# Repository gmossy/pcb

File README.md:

# pcb

This repository contains my printed circuit board designs. I use many of the designs for my robot projects and some of the others for general purposes and smaller electronics projects.

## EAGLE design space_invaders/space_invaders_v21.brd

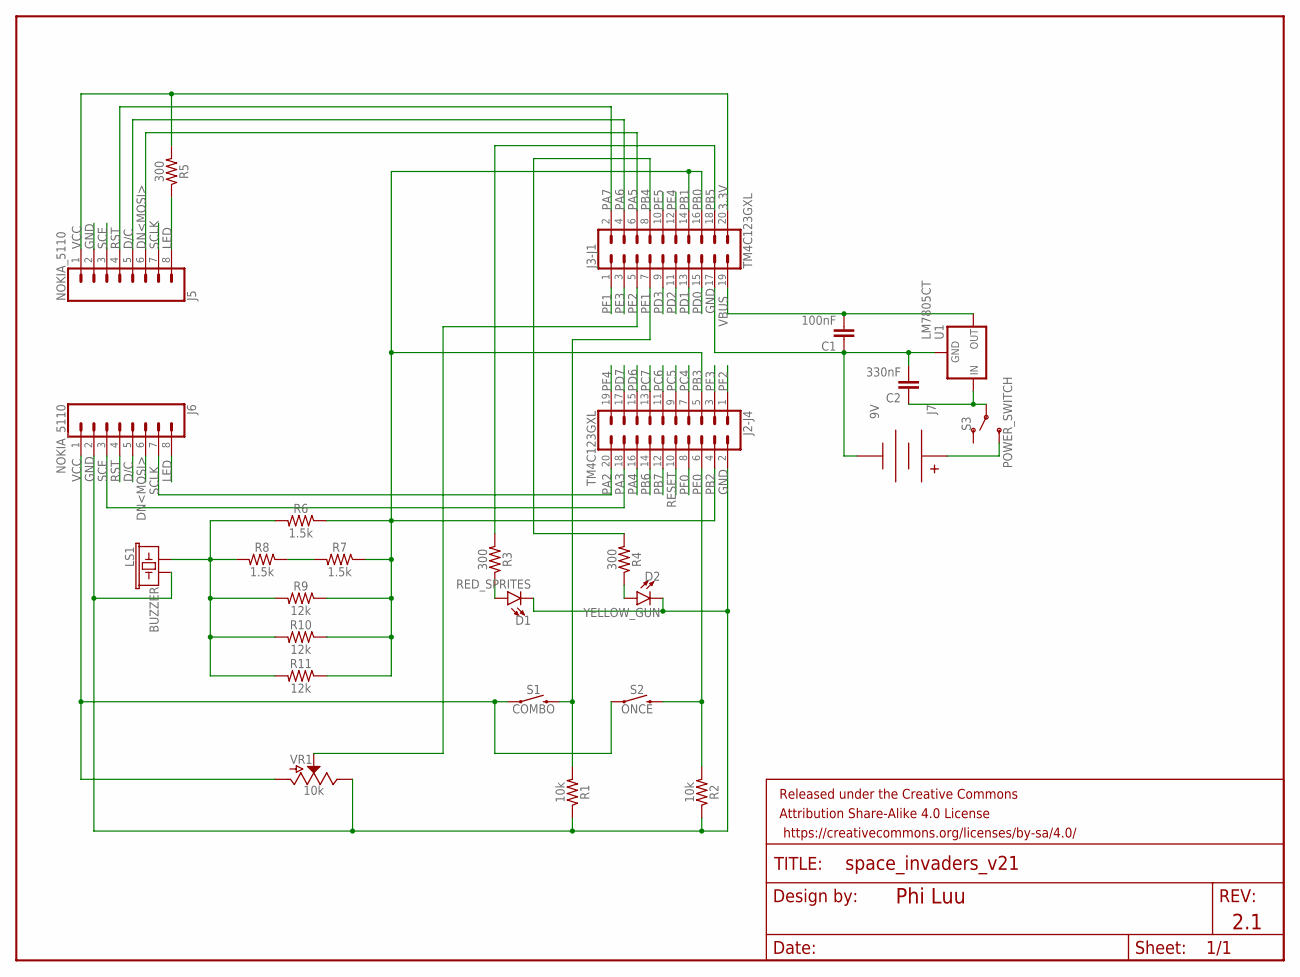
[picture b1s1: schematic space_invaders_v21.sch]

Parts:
C1: 100nF; CAP-PTH-SMALL-KIT
C2: 330nF; CAP-PTH-SMALL-KIT
D1: RED_SPRITES; LED_5MM
D2: YELLOW_GUN; LED_5MM
FRAME1: FRAME-LETTER; CREATIVE_COMMONS
J2-J4, J3-J1: TM4C123GXL; 2X10
J5, J6: NOKIA_5110; 1X08
J7: 9V; BC9VPC
LS1: BUZZER; BUZZER-12MM
R1, R2: 10k; AXIAL-0.3
R3, R4, R5: 300; AXIAL-0.3
R6, R7, R8: 1.5k; AXIAL-0.3
R9, R10, R11: 12k; AXIAL-0.3
S1: COMBO; TACTILE_SWITCH_PTH_6.0MM
S2: ONCE; TACTILE_SWITCH_PTH_6.0MM
S3: POWER_SWITCH; SWITCH_SPDT_PTH_11.6X4.0MM
U1: LM7805CT; TO220-IGO
VR1: 10k; SLIDER-MEDIUM

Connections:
3.3V: J3-J1.20, J5.1, J6.1, R5.P$2 (2), S1.1, S2.1, VR1.BOTTOM (A)
9V: J7.V+, S3.3 (S)
DAC: J2-J4.4, J2-J4.5, J3-J1.14, J3-J1.16, R6.P$1 (1), R7.P$1 (1), R9.P$1 (1), R10.P$1 (1), R11.P$1 (1)
DAC_OUT: LS1.+ (1), R6.P$2 (2), R8.P$2 (2), R9.P$2 (2), R10.P$2 (2), R11.P$2 (2)
GND: C1.1, C2.2, D1.K (C), D2.K (C), J2-J4.2, J3-J1.17, J5.2, J6.2, J7.V-, LS1.- (2), R1.P$1 (1), R2.P$1 (1), U1.GND, VR1.TOP (E)
LED: J5.8, J6.8, R5.P$1 (1)
LLED: D1.A, R3.P$1 (1)
unnamed: R7.P$2 (2), R8.P$1 (1)
PA2: J2-J4.20, J5.7, J6.7
PA3: J2-J4.18, J5.3, J6.3
PA4: J2-J4.16
PA5: J3-J1.6, J5.6, J6.6
PA6: J3-J1.4, J5.5, J6.5
PA7: J3-J1.2, J5.4, J6.4
PB4: J3-J1.8, R4.P$2 (2)
PB5: J3-J1.18, R3.P$2 (2)
PB6: J2-J4.14
PB7: J2-J4.12
PC4: J2-J4.7
PC5: J2-J4.9
PC6: J2-J4.11
PC7: J2-J4.13
PD0: J3-J1.15
PD1: J3-J1.13
PD2: J3-J1.11
PD3: J3-J1.9
PD6: J2-J4.15
PD7: J2-J4.17
PE0: J2-J4.6, R2.P$2 (2), S2.3 (2)
PE1: J3-J1.7, R1.P$2 (2), S1.3 (2)
PE2: J3-J1.5, VR1.WIPER (S)
PE3: J3-J1.3
PE4: J3-J1.12
PE5: J3-J1.10
PF0: J2-J4.8
PF1: J3-J1.1
PF2: J2-J4.1
PF3: J2-J4.3
PF4: J2-J4.19
RESET: J2-J4.10
RLED: D2.A, R4.P$1 (1)
VBUS: C1.2, J3-J1.19, U1.OUT
VIN: C2.1, S3.2, U1.IN

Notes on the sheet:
Phi Luu
2.1
PB0
PB1
PB3
VCC
RST
D/C
DN<MOSI>
SCE
SCLK
PB2

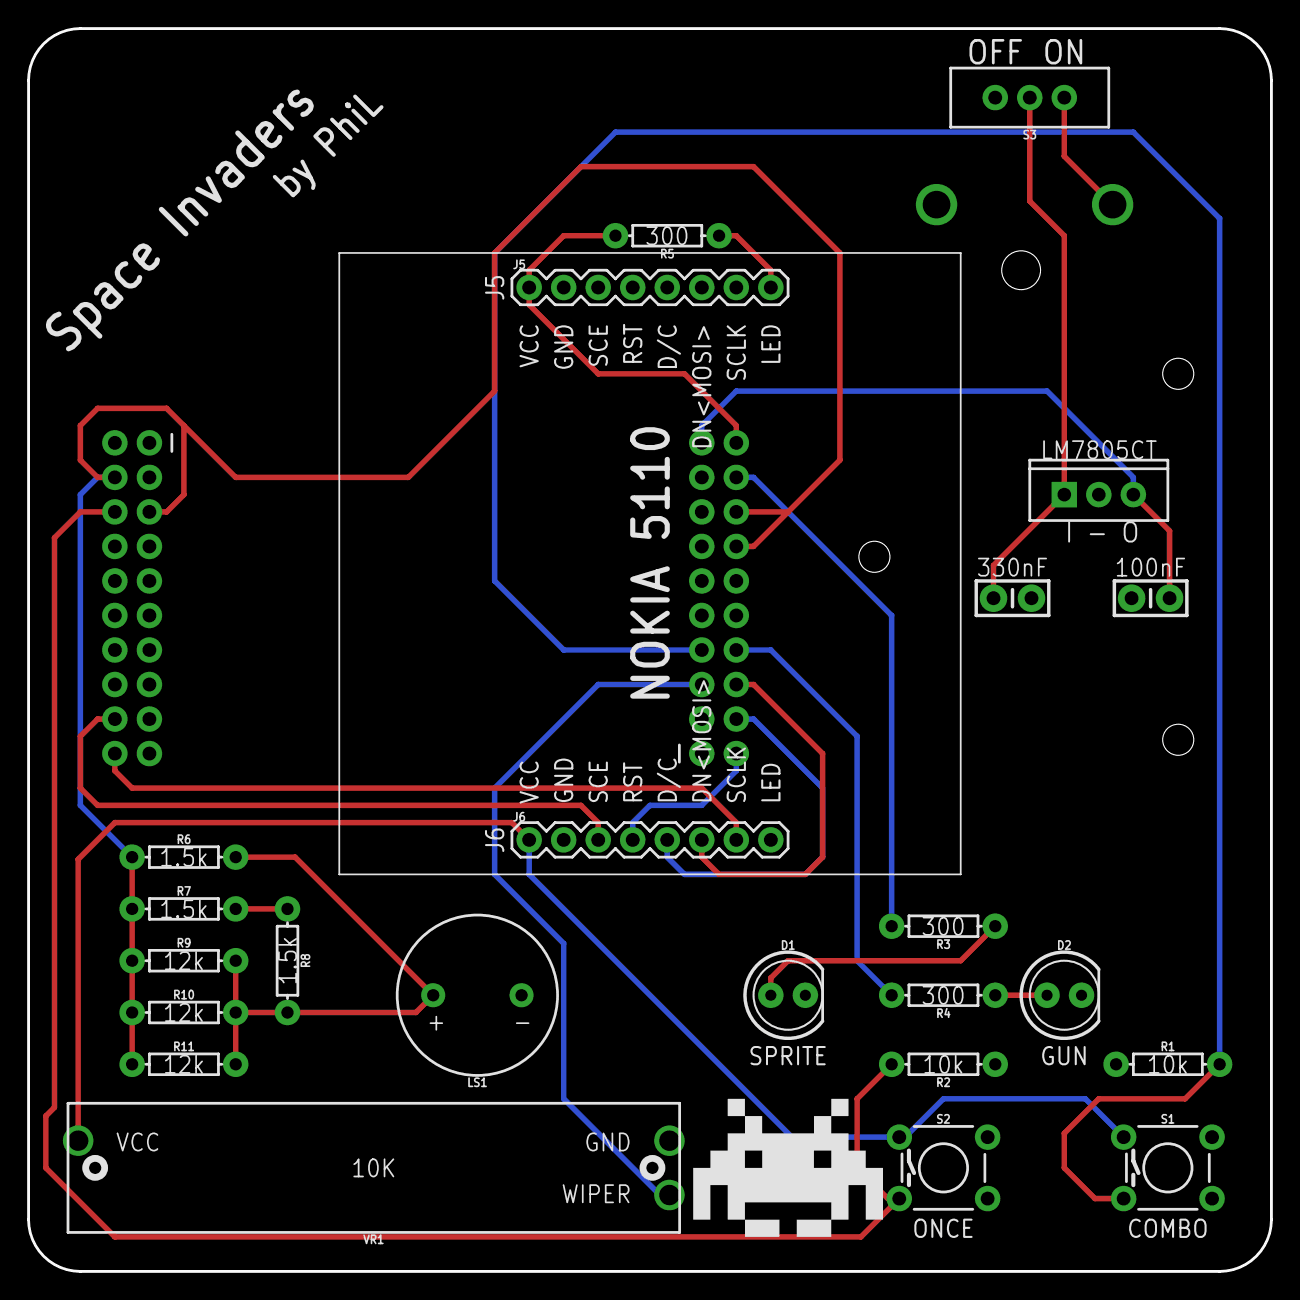
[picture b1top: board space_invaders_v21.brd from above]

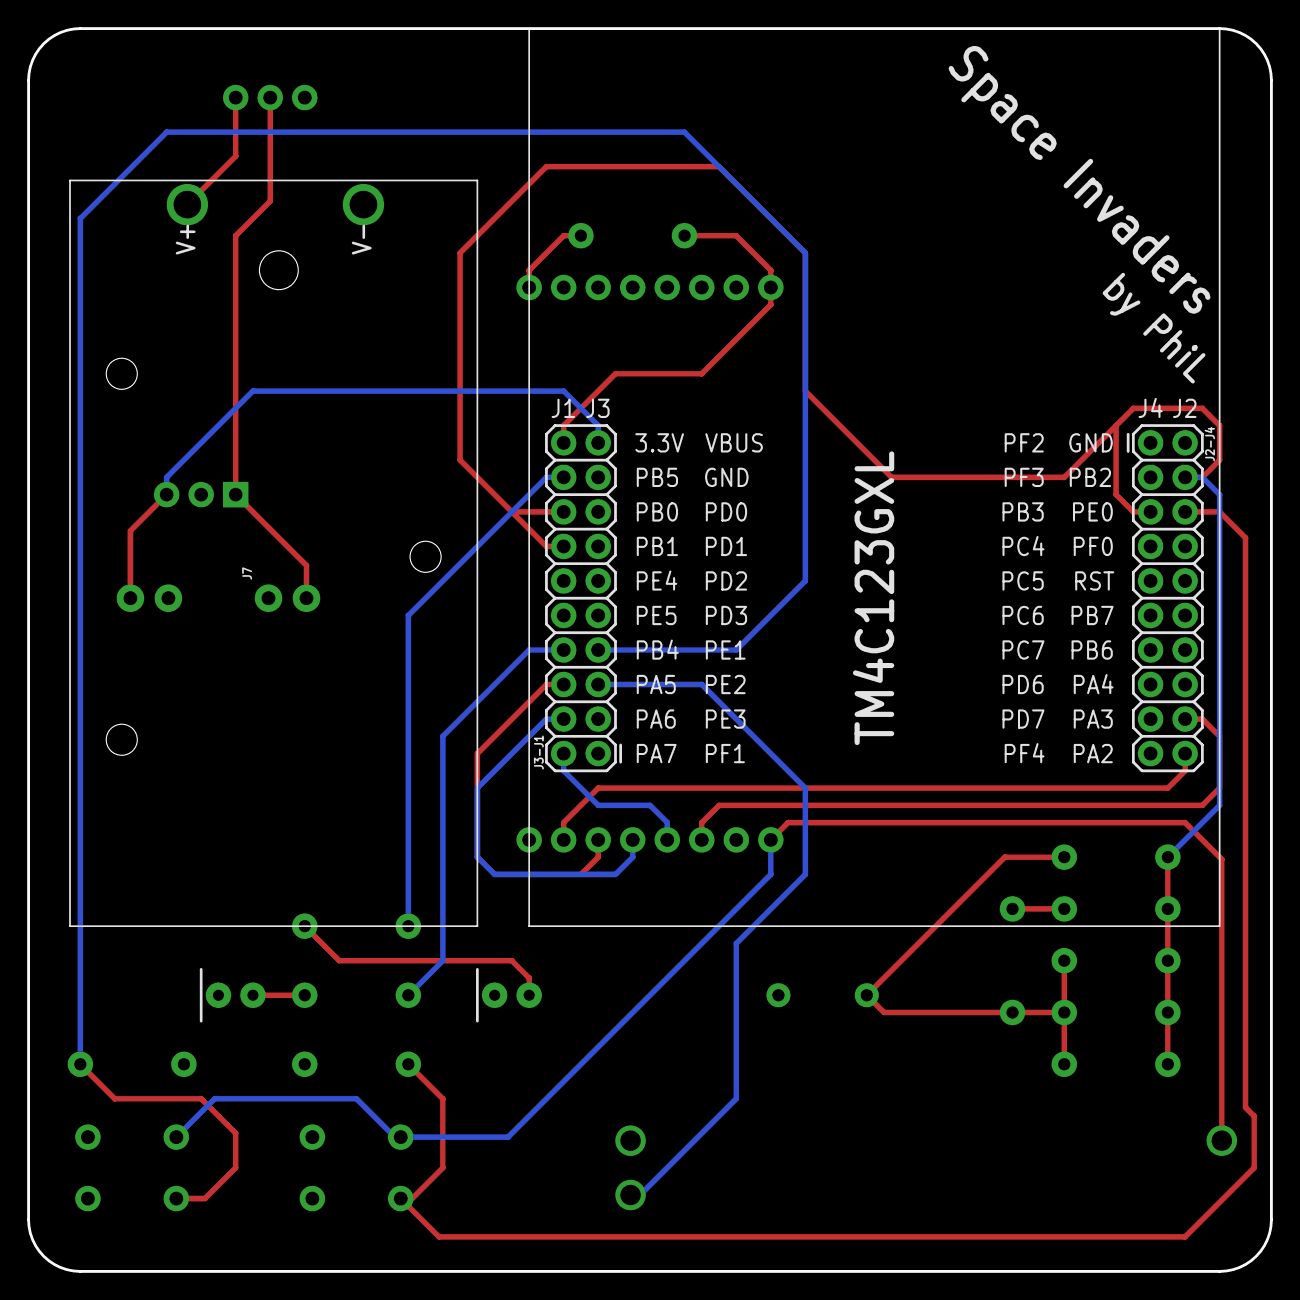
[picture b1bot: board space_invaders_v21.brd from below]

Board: 2 copper layers, 91.4 x 91.4 mm, 27 parts (3 on the bottom side), 21 nets.

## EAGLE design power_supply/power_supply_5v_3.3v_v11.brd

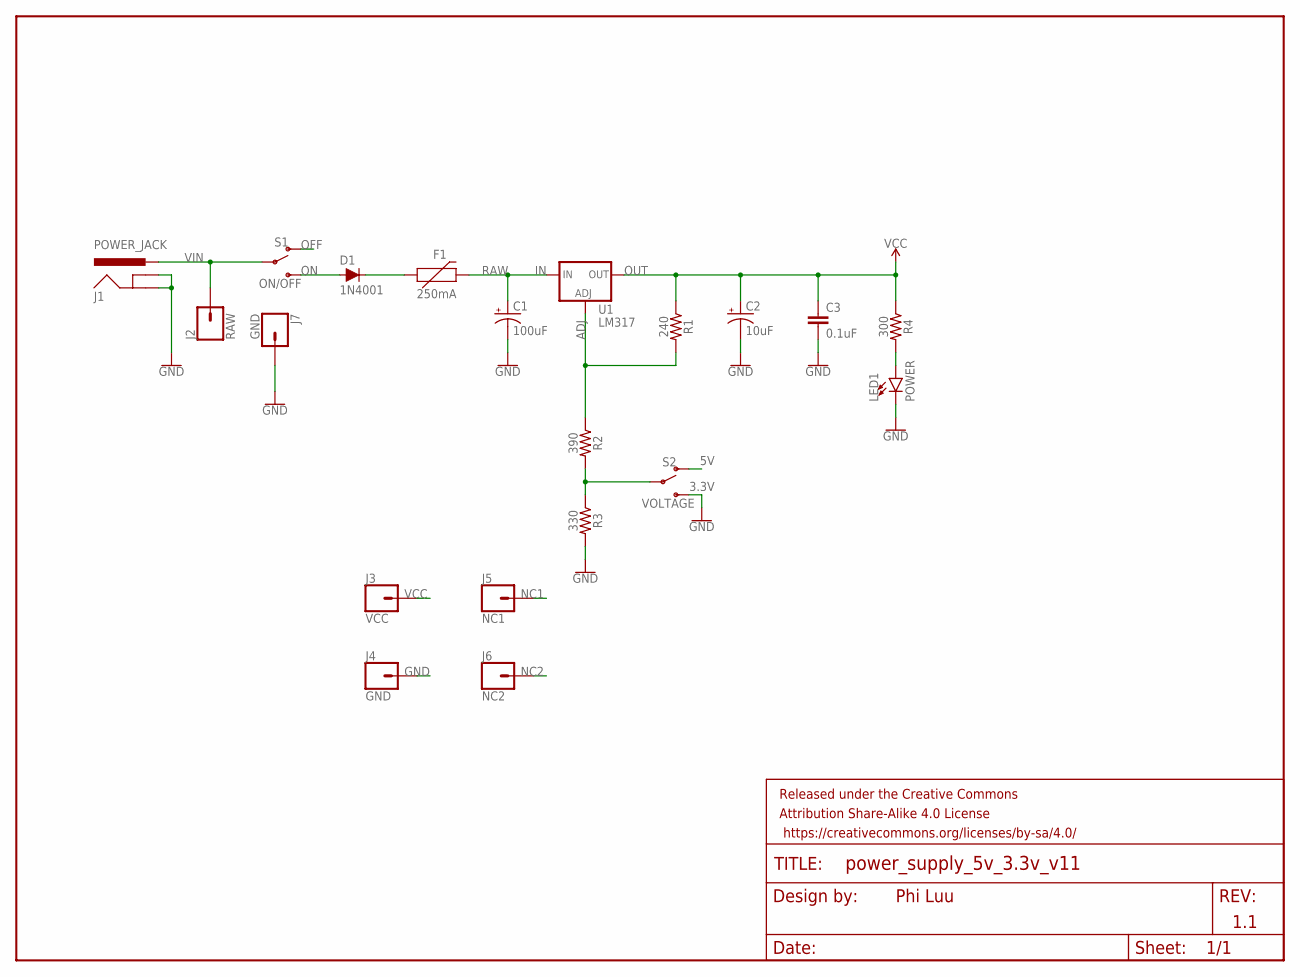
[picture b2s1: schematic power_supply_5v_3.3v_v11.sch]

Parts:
C1: 100uF; CPOL-RADIAL-2.5MM-6.5MM
C2: 10uF; CPOL-RADIAL-2.5MM-5MM
C3: 0.1uF; CAP-PTH-SMALL-KIT
D1: 1N4001; DIODE-1N4001
F1: 250mA; PTH
FRAME1: FRAME-LETTER; CREATIVE_COMMONS
J1: POWER_JACK; POWER_JACK_PTH
J2: RAW; 1X01
J3: VCC; 1X01
J4, J7: GND; 1X01
J5: NC1; 1X01
J6: NC2; 1X01
LED1: POWER; LED_5MM
R1: 240; AXIAL-0.3
R2: 390; AXIAL-0.3
R3: 330; AXIAL-0.3
R4: 300; AXIAL-0.3
S1: ON/OFF; SWITCH_SPDT_PTH_11.6X4.0MM
S2: VOLTAGE; SWITCH_SPDT_PTH_11.6X4.0MM
U1: LM317; TO220-ADJ

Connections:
5V: S2.1 (O)
ADJ: R1.P$2 (2), R2.P$1 (1), U1.ADJ
GND: C1.2 (-), C2.2 (-), C3.2, J1.GND, J1.GNDBREAK, J4.1, J7.1, LED1.K (C), R3.P$2 (2), S2.3 (S)
LED: LED1.A, R4.P$2 (2)
unnamed: D1.C, F1.P$1 (1)
unnamed: R2.P$2 (2), R3.P$1 (1), S2.2
NC1: J5.1
NC2: J6.1
OFF: S1.1 (O)
ON: D1.A, S1.3 (S)
RAW: C1.1 (+), F1.P$2 (2), U1.IN
VCC: C2.1 (+), C3.1, J3.1, R1.P$1 (1), R4.P$1 (1), U1.OUT
VIN: J1.PWR, J2.1, S1.2

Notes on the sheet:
Phi Luu
1.1
OUT
3.3V

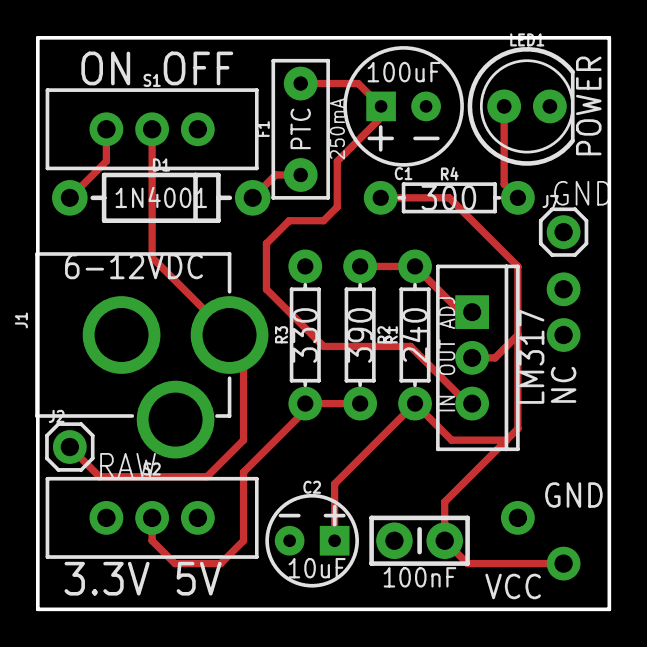
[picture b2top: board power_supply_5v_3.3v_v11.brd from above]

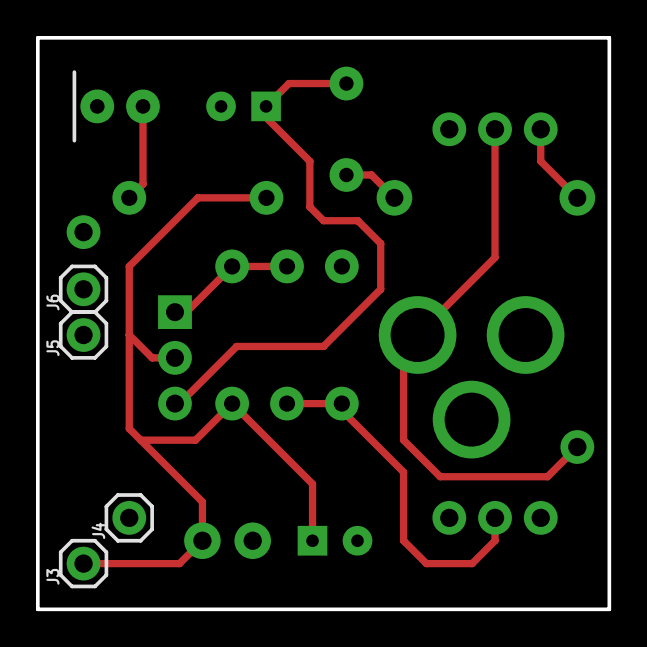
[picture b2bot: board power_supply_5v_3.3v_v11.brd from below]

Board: 2 copper layers, 31.8 x 31.8 mm, 21 parts (4 on the bottom side), 9 nets.

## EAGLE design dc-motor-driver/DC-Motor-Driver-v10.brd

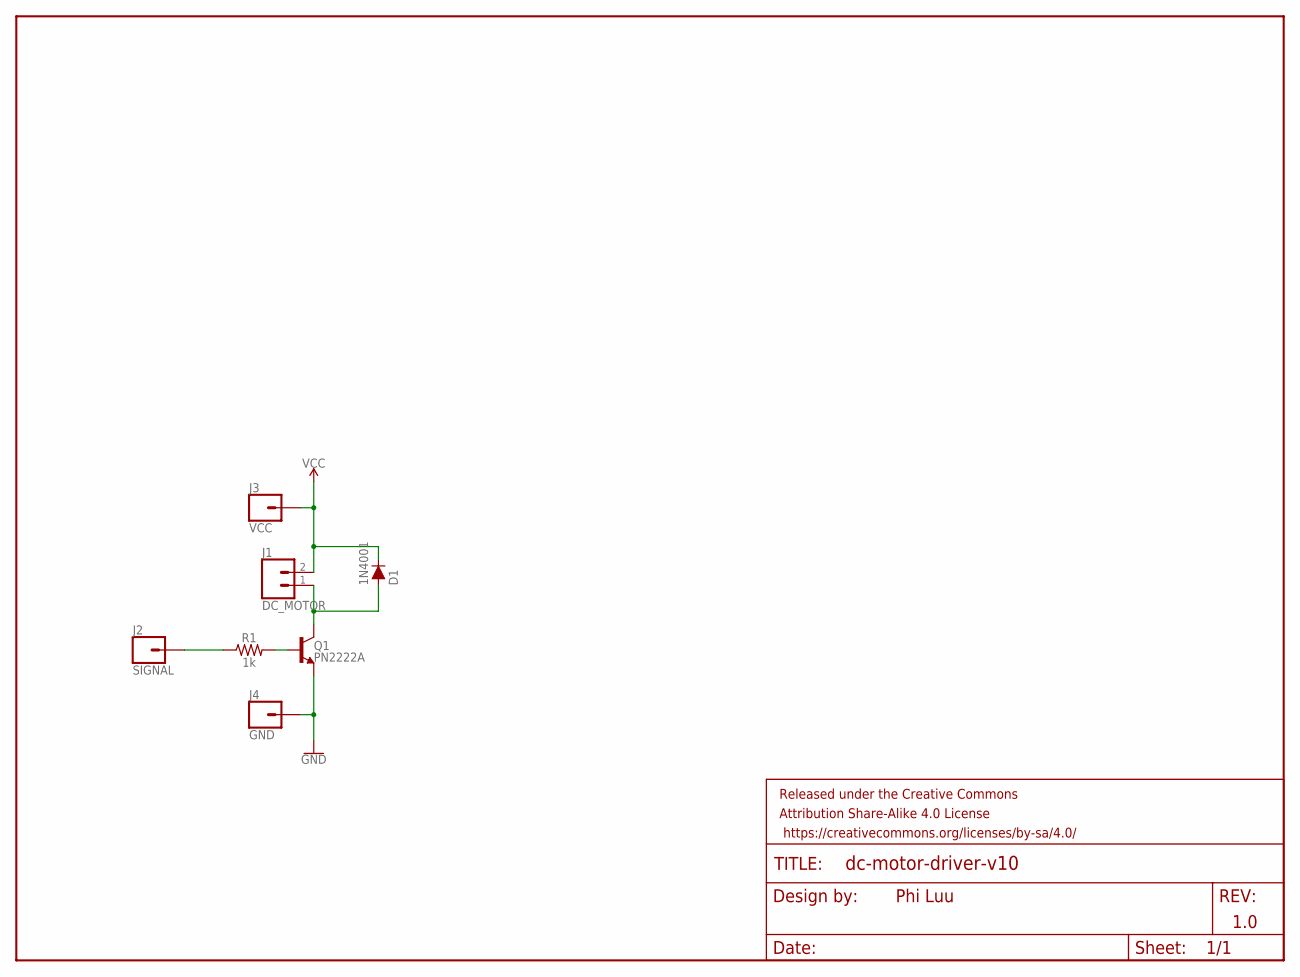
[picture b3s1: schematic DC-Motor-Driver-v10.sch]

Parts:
D1: 1N4001; DIODE-1N4001
FRAME1: FRAME-LETTER; CREATIVE_COMMONS
J1: DC_MOTOR; 1X02
J2: SIGNAL; 1X01
J3: VCC; 1X01
J4: GND; 1X01
Q1: PN2222A; TO-92
R1: 1k; AXIAL-0.3

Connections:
BASE: Q1.2 (B), R1.P$2 (2)
COLLECTOR: D1.A, J1.1, Q1.1 (C)
GND: J4.1, Q1.3 (E)
SIGNAL: J2.1, R1.P$1 (1)
VCC: D1.C, J1.2, J3.1

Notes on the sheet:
Phi Luu
1.0

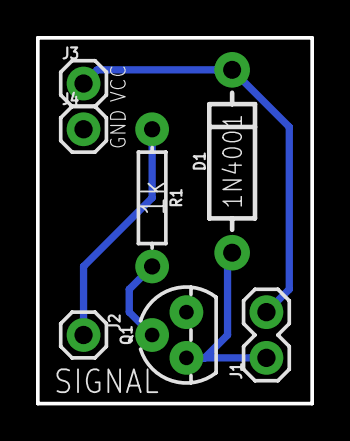
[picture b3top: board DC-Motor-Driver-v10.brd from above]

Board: 2 copper layers, 15.2 x 20.3 mm, 8 parts (0 on the bottom side), 5 nets.

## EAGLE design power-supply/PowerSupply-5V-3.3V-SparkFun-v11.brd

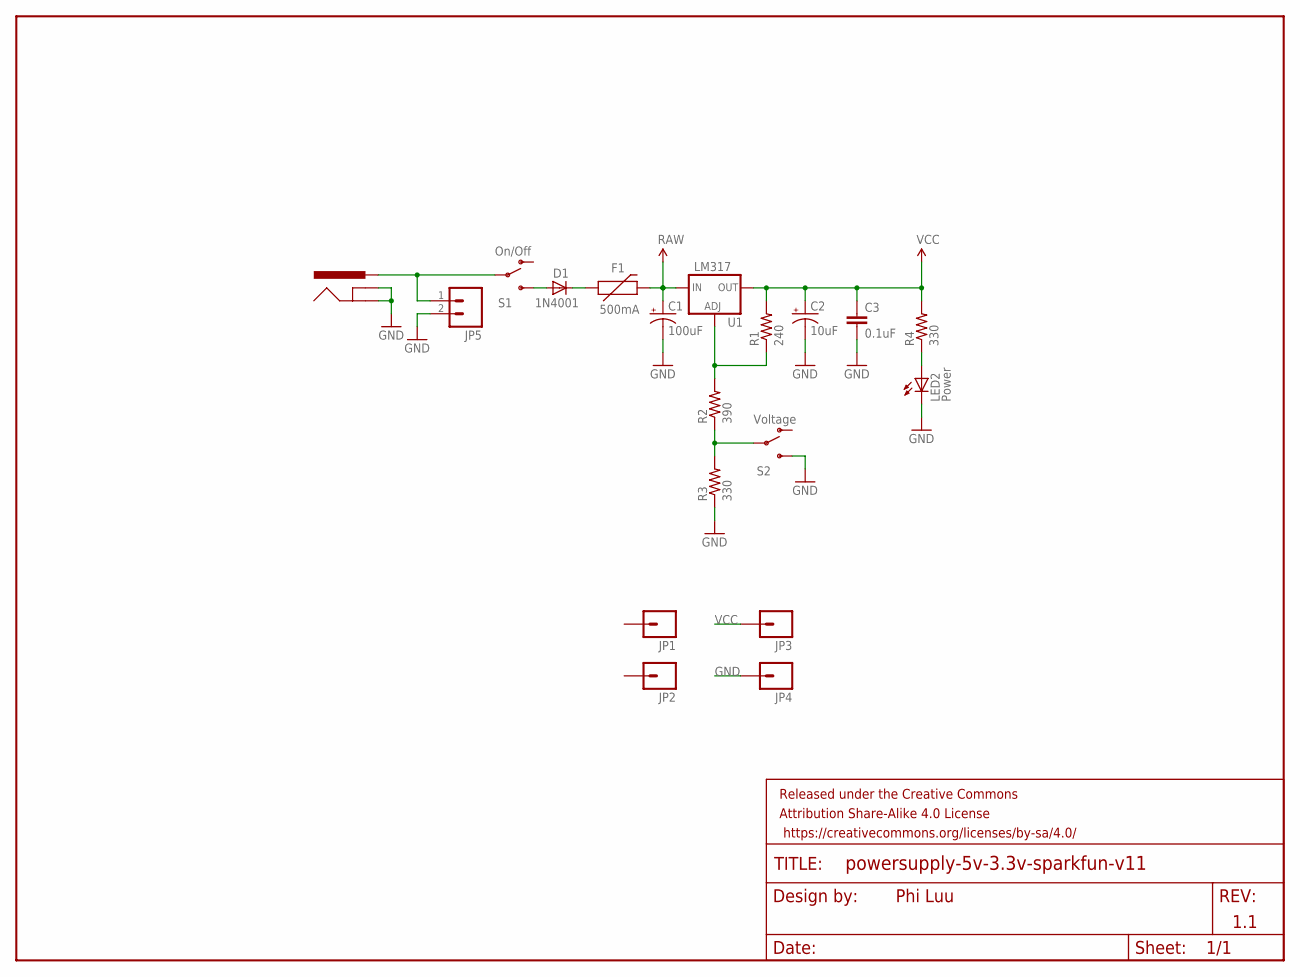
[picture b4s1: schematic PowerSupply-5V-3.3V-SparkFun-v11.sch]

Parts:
C1: 100uF; CPOL-RADIAL-100UF-25V
C2: 10uF; CPOL-RADIAL-10UF-25V
C3: 0.1uF; CAP-PTH-SMALL2
D1: 1N4001; DIODE-0.4
F1: 500mA; PTC
FRAME1: FRAME-LETTER; CREATIVE_COMMONS
J1: POWER_JACKPTH; POWER_JACK_PTH
JP1, JP2, JP3, JP4: M01PTH; 1X01
JP5: M02PTH; 1X02
LED2: Power; LED5MM
R1: 240; AXIAL-0.3
R2: 390; AXIAL-0.3
R3, R4: 330; AXIAL-0.3
S1: On/Off; SWITCH-SPST
S2: Voltage; SWITCH-SPST
U1: LM317; TO220-ADJ

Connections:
GND: C1.2 (-), C2.2 (-), C3.2, J1.GND, J1.GNDBREAK, JP4.1, JP5.2, LED2.K (C), R3.P$1 (1), S2.3 (S)
unnamed: D1.C, F1.P$1 (1)
unnamed: D1.A, S1.3 (S)
unnamed: J1.PWR, JP5.1, S1.2
unnamed: R2.P$1 (1), R3.P$2 (2), S2.2
unnamed: R1.P$1 (1), R2.P$2 (2), U1.ADJ
unnamed: LED2.A, R4.P$1 (1)
RAW: C1.1 (+), F1.P$2 (2), U1.IN
VCC: C2.1 (+), C3.1, JP3.1, R1.P$2 (2), R4.P$2 (2), U1.OUT

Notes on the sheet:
1.1
Phi Luu

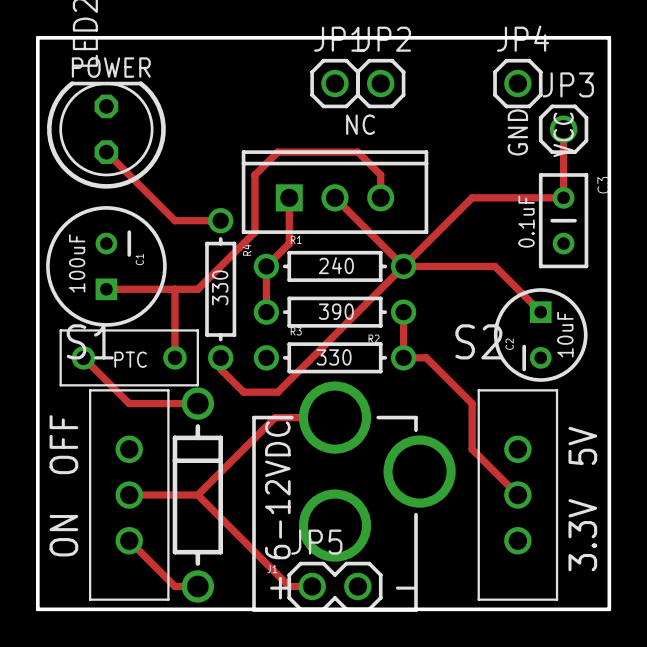
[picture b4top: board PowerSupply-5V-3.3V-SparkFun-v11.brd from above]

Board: 2 copper layers, 31.8 x 31.8 mm, 20 parts (0 on the bottom side), 9 nets.

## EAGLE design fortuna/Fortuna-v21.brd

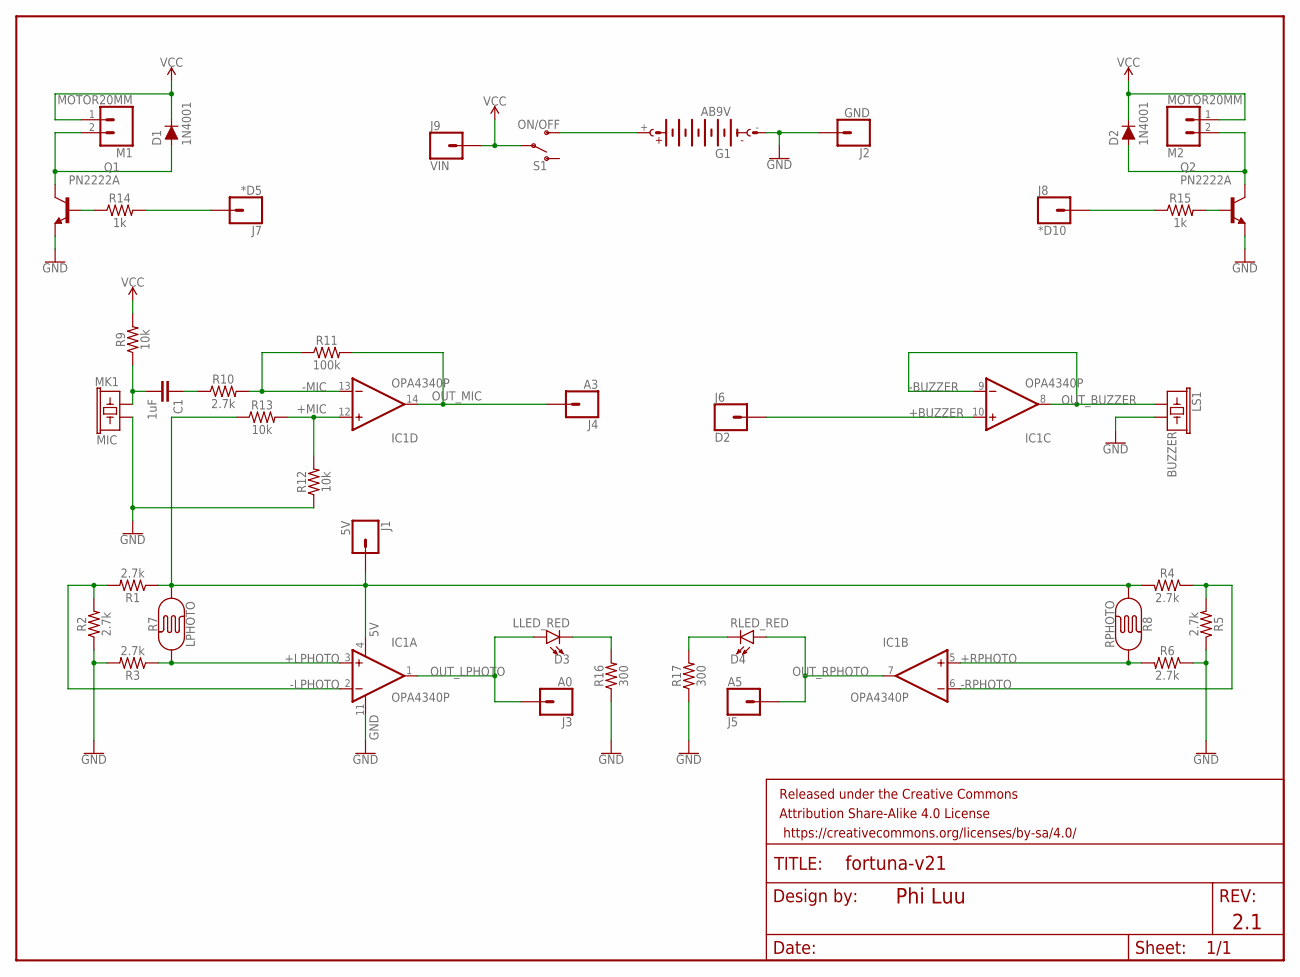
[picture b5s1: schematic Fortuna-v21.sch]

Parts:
C1: 1uF; CAP-PTH-SMALL-KIT
D1, D2: 1N4001; DIODE-1N4001
D3: LLED_RED; LED_5MM
D4: RLED_RED; LED_5MM
FRAME1: FRAME-LETTER; CREATIVE_COMMONS
G1: AB9V
IC1: OPA4340P; DIL14
J1: 5V; 1X01
J2: GND; 1X01
J3: A0; 1X01
J4: A3; 1X01
J5: A5; 1X01
J6: D2; 1X01
J7: *D5; 1X01
J8: *D10; 1X01
J9: VIN; 1X01
LS1: BUZZER; BUZZER-12MM
M1, M2: MOTOR20MM; 1X02
MK1: MIC; MICROPHONE-PTH-9.7MM
Q1, Q2: PN2222A; TO92-EBC-OVAL
R1, R2, R3, R4, R5, R6, R10: 2.7k; AXIAL-0.3
R7: LPHOTO; PHOTOCELL
R8: RPHOTO; PHOTOCELL
R9, R12, R13: 10k; AXIAL-0.3
R11: 100k; AXIAL-0.3
R14, R15: 1k; AXIAL-0.3
R16, R17: 300; AXIAL-0.3
S1: ON/OFF; SWITCH_SPDT_PTH_11.6X4.0MM

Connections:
5V: IC1.4 (V+), J1.1, R1.P$1 (1), R4.P$2 (2), R7.2, R8.2, R13.P$1 (1)
9V: G1.+, S1.3 (S)
+LPHOTO: IC1.3 (+IN), R3.P$1 (1), R7.1
+MIC: IC1.12 (+IN), R12.P$2 (2), R13.P$2 (2)
+RPHOTO: IC1.5 (+IN), R6.P$2 (2), R8.1
-LPHOTO: IC1.2 (-IN), R1.P$2 (2), R2.P$2 (2)
-MIC: IC1.13 (-IN), R10.P$2 (2), R11.P$1 (1)
-RPHOTO: IC1.6 (-IN), R4.P$1 (1), R5.P$2 (2)
D2: IC1.10 (+IN), J6.1
GND: G1.-, IC1.11 (V-), J2.1, LS1.- (2), MK1.GND (2), Q1.E, Q2.E, R2.P$1 (1), R3.P$2 (2), R5.P$1 (1), R6.P$1 (1), R12.P$1 (1), R16.P$1 (1), R17.P$1 (1)
unnamed: C1.2, MK1.OUT (1), R9.P$1 (1)
unnamed: C1.1, R10.P$1 (1)
unnamed: D3.K (C), R16.P$2 (2)
unnamed: D4.K (C), R17.P$2 (2)
unnamed: Q1.B, R14.P$1 (1)
unnamed: D1.A, M1.2, Q1.C
unnamed: D2.A, M2.2, Q2.C
unnamed: Q2.B, R15.P$2 (2)
OUT_BUZZER: IC1.8 (OUT), IC1.9 (-IN), LS1.+ (1)
OUT_LMOTOR: J7.1, R14.P$2 (2)
OUT_LPHOTO: D3.A, IC1.1 (OUT), J3.1
OUT_MIC: IC1.14 (OUT), J4.1, R11.P$2 (2)
OUT_RMOTOR: J8.1, R15.P$1 (1)
OUT_RPHOTO: D4.A, IC1.7 (OUT), J5.1
VCC: D1.C, D2.C, J9.1, M1.1, M2.1, R9.P$2 (2), S1.2

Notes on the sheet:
Phi Luu
2.1
+BUZZER
-BUZZER

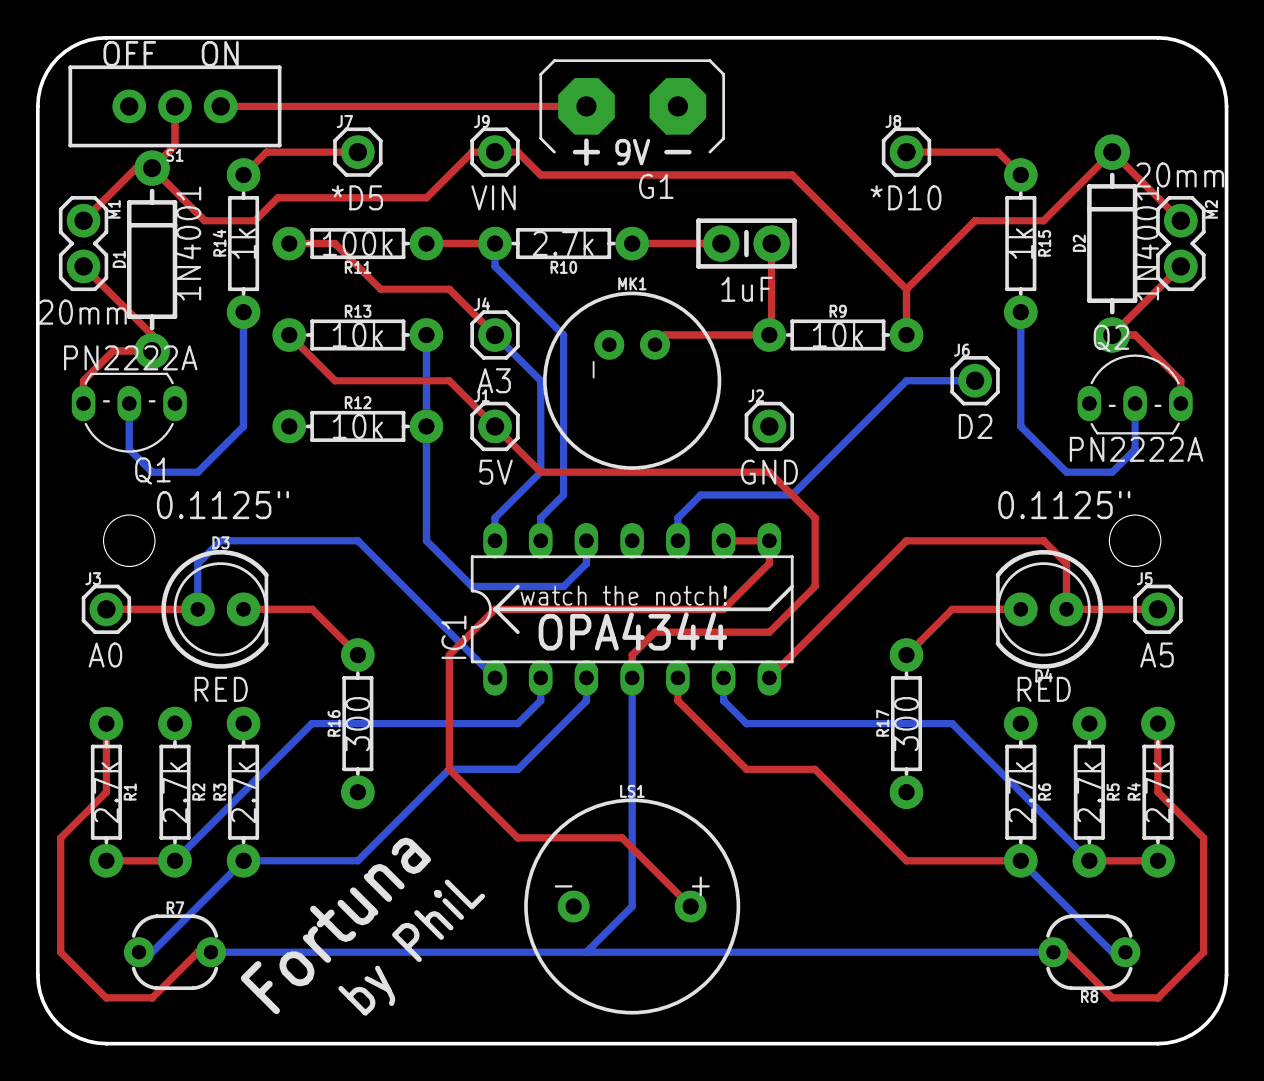
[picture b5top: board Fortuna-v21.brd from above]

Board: 2 copper layers, 66.0 x 55.9 mm, 41 parts (0 on the bottom side), 25 nets.

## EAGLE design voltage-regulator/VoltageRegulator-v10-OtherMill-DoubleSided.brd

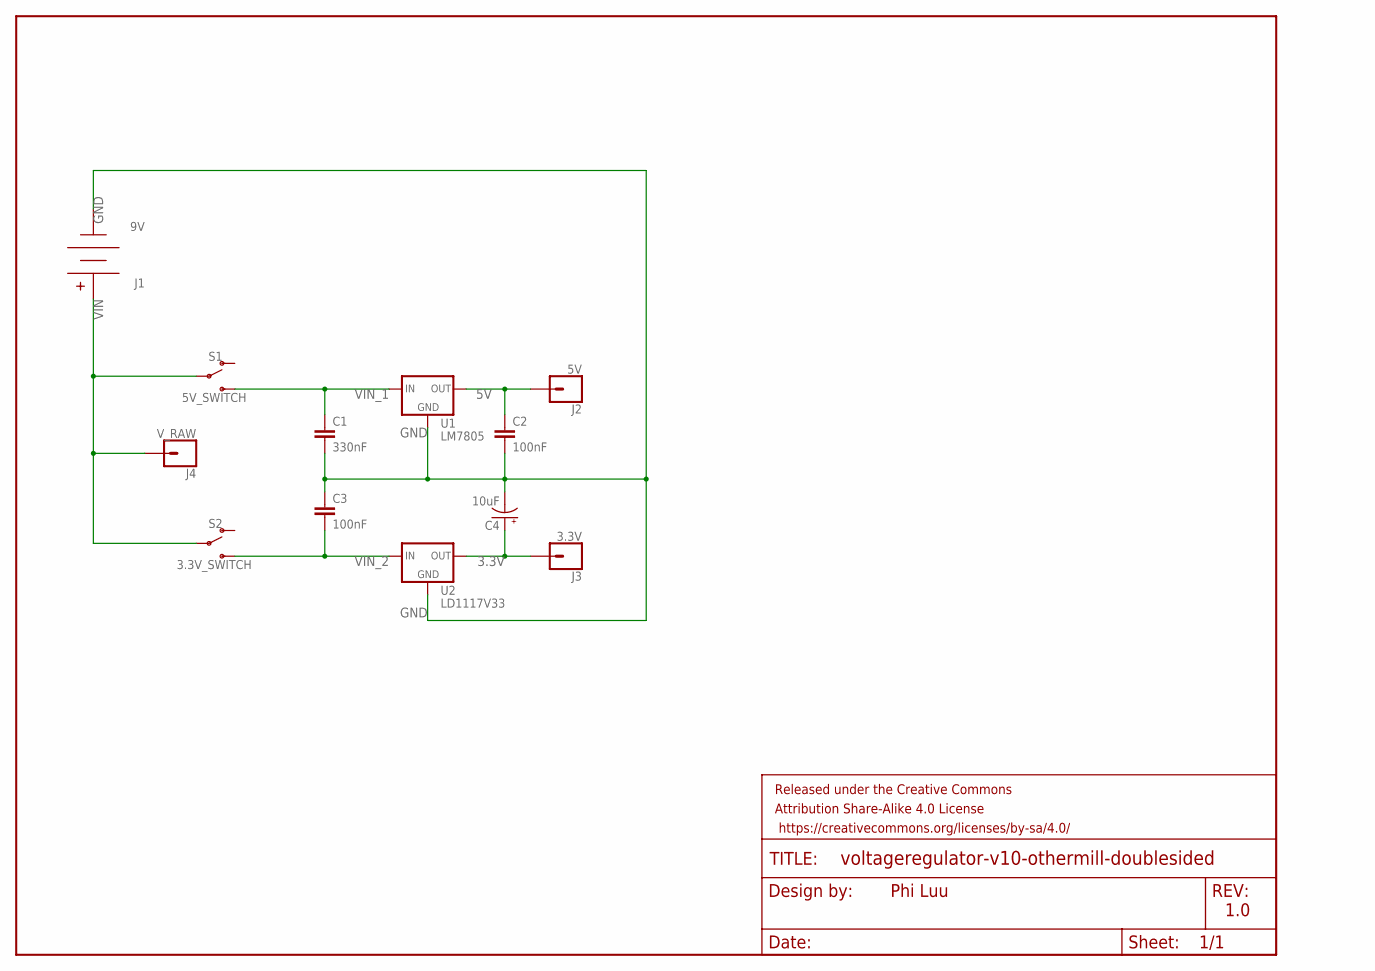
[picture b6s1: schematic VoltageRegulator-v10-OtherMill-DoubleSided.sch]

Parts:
C1: 330nF; CAP-PTH-SMALL-KIT
C2, C3: 100nF; CAP-PTH-SMALL-KIT
C4: 10uF; CPOL-RADIAL-2.5MM-5MM
FRAME1: FRAME-LETTER; CREATIVE_COMMONS
J1: 9V; BC9VPC
J2: 5V; 1X01
J3: 3.3V; 1X01
J4: V_RAW; 1X01
S1: 5V_SWITCH; SWITCH_SPDT_PTH_11.6X4.0MM
S2: 3.3V_SWITCH; SWITCH_SPDT_PTH_11.6X4.0MM
U1: LM7805; TO-220-ALT
U2: LD1117V33; 78XXL

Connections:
3.3V: C4.1 (+), J3.1, U2.GND (OUT)
5V: C2.1, J2.1, U1.OUT
GND: C1.2, C2.2, C3.1, C4.2 (-), J1.V-, U1.GND, U2.IN (GND)
VIN: J1.V+, J4.1, S1.2, S2.2
VIN_1: C1.1, S1.3 (S), U1.IN
VIN_2: C3.2, S2.3 (S), U2.OUT (IN)

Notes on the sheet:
Phi Luu
1.0

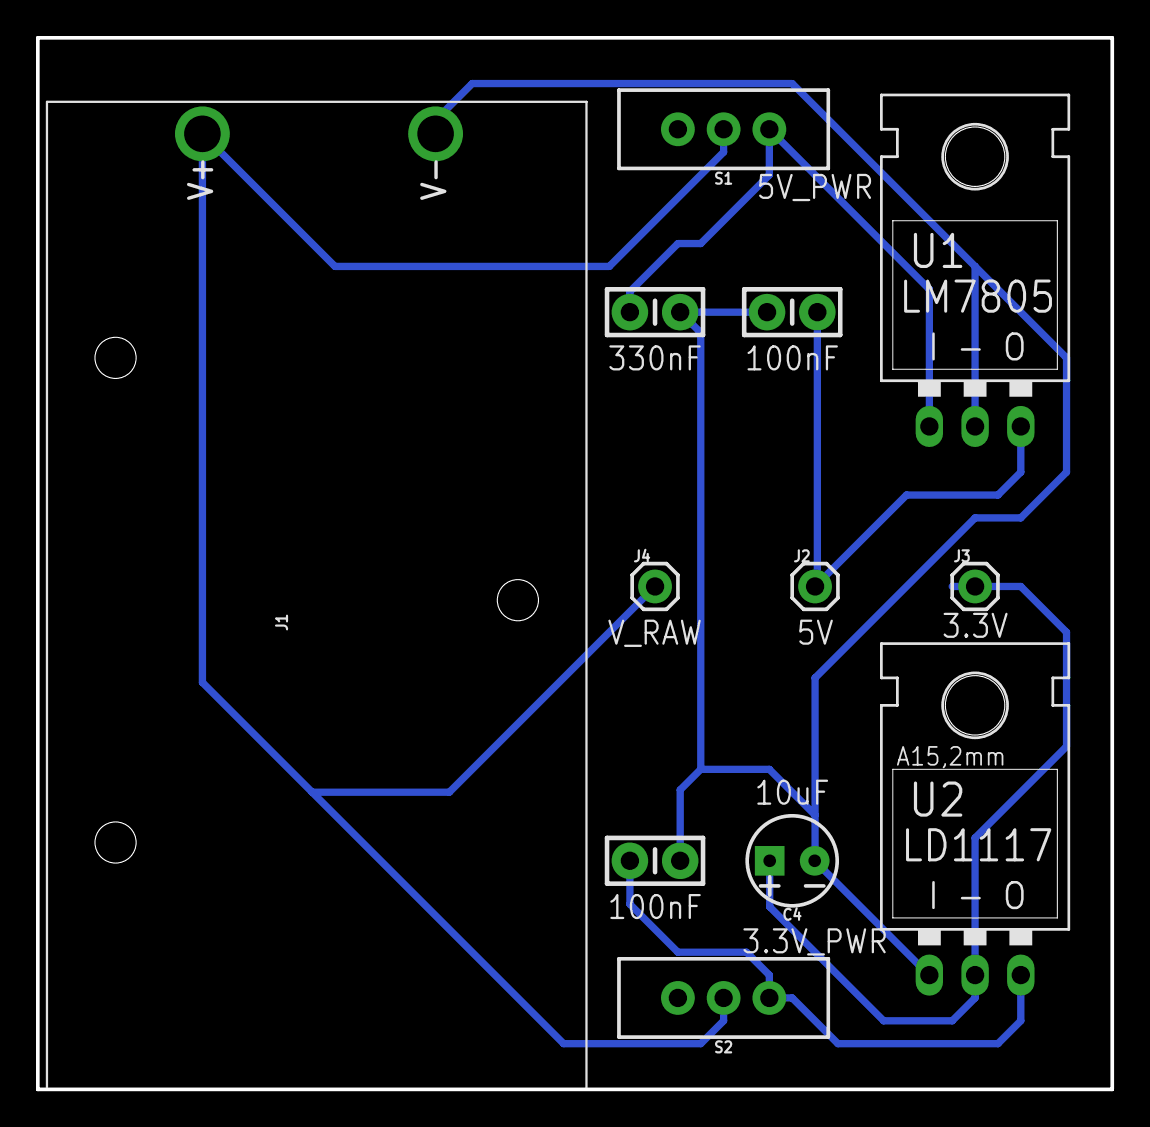
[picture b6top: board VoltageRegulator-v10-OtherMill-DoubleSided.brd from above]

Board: 2 copper layers, 59.7 x 58.4 mm, 13 parts (0 on the bottom side), 6 nets.

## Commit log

2017-02-01 :octocat: Added .gitattributes & .gitignore files
2017-02-01 Create & Edit .gitignore
    Ignore unnecessary EAGLE and OS files
2017-02-01 Create workplace & Initiate projects
2017-02-05 Complete board - SpaceInvaders 2.0
2017-02-05 Add silkscreen & Finish SpaceInvaders
2017-02-05 Finish fortuna schematic
2017-02-05 Reorganize workplace
2017-02-07 Remove cam
2017-02-07 Add Design Rule Check (DRC) for OtherMill CNC
2017-02-07 Add CAM jobs
2017-02-07 Add SparkFun Design Rule Check
2017-02-07 Setup SpaceInvaders regular manufacturing
    Default EAGLE Design Rule Check (DRC). Double sided.
2017-02-07 Setup SpaceInvaders OtherMill. Bottom traces only.
    Setup PCB compatible with OtherMill Pro Design Rule Check (DRC). Single
    sided and bottom only.
2017-02-07 Setup SpaceInvaders OtherMill. Top traces only.
    Setup PCB compatible with OtherMill Pro Design Rule Check (DRC). Single
    sided and top only.
2017-02-10 Remove Top layer & Edit Bottom layer
2017-02-12 Edit SparkFun CAM and DRC
2017-02-12 Update board SpaceInvaders
    Add names to empty pins
    Naming convention
    Change switch package
2017-02-12 Change battery Fortuna
2017-02-12 Initiate BareBonnesArduino
2017-02-12 Follow naming convention - English letter only
2017-02-12 Suspend board layout of BareBonesArduino
2017-02-12 Reposition SpaceInvaders board layout
2017-02-13 Finish BareBonesArduino for manufacturing
2017-02-13 Create OtherMill-compatible BareBonesArduino
2017-02-13 Finish SpaceInvaders v2.0 for manufacturing
2017-02-13 Create OtherMill-compatible SpaceInvaders
2017-02-16 Change LLED and RLED resistor value from 300 to 220
2017-02-17 Reposition components BareBonesArduino
2017-02-17 Minimize the size of SpaceInvaders
2017-02-17 Add versions
2017-02-17 Rip off Autorouter. Will route by hand.
2017-02-18 Connect nets & Apply schematic convention
2017-02-19 Expand & make more space in schematic
2017-02-21 Route SpaceInvaders Manually - SpaceInvaders v3.0
2017-03-03 Remove CAM-job files
2017-03-03 Minimize the board area to 3.60" x 3.60"
2017-03-05 Remove CAM files
2017-03-05 Add versions to file names & Edit stuff
    Add versions to file names.
    Center Nokia5110 & Edit traces thereof.
    Add holes for 9V battery's wires to come through.
    v2.1: Replace "SpaceInvaders," "by PhiL," and the sprite icon by Top &
    Bottom layers.
2017-03-06 Change the final version to 2.1
    v3.0 and v2.1 are the same in structure. The only difference is that one
    is supposed to made professionally by a fabrication house and the other
    one is made by OtherMill.
2017-03-06 Design board layout for Fortuna - v2.1
2017-03-08 Add SPDT power switch
2017-03-11 Fillet corners of the boards
2017-03-11 Change pin position SPDT slide switch
2017-03-17 Change name - Bottom layer only
2017-03-17 Change trace widths (See description)
    netclass power: width = 0.018" = 18 mil
    netclass default: width = 0.016" = 16 mil
2017-03-17 Add drill holes to keep board on the robot
2017-03-17 Change traces widths (see description)
    netclass power: change to 0.018" (18 mil)
    netclass default: change to 0.016" (16 mil)
2017-03-19 Add GND to RATSNEST
2017-03-19 Change project's name & Add SparkFun Power Supply Design
2017-03-19 Make SparkFun-like power supply
2017-03-19 Separate OtherMill versions & Edit copper pour
    Separate OtherMIll versions from the default fab-house versions.
    Bottom copper-pour layer for OtherMill versions
    Top & Bottom copper-pour layers for default fab-house versions.
2017-03-19 Add raw voltage source
2017-03-24 Make major bottom layer (see description)
    Since OtherMill just mills the board but doesn't pour copper over the
    holes. The top and the bottom layer of a vias are disconnected. In order
    to reduce the hard word in soldering, I brough all traces to the bottom
    layer & set copper pour for both sides of the board.
2017-03-31 Edit trivial parts for Space Invaders
2017-03-31 Create Barebones Arduino
2017-05-10 Design DC motor driver circuit - v1.0
2017-06-22 Edit .gitignore & Add README.md
2017-06-22 Add GoPiGo robot Mod Schematic
2017-06-23 Edit naming style
    File names:
    Replace hyphens with underscores.
    All lowercase letters.
2017-06-29 Add arduino schematics
2017-06-29 Add schematics from Raspberry Pi repo
2017-06-29 Make change to the GoPiGo Mod schematic (simplification)
2017-06-29 Add Fritzing project from arduino repo
2017-06-30 Move Fritzing project from robots repo to here
2017-08-21 Name the robot: fidget
2017-09-24 Add MIT License
2017-09-24 Update MIT License
2017-11-15 Remove MIT License
2017-11-15 Create MIT License
2018-01-14 Add Linux & macOS
2018-02-07 Ignore .vscode

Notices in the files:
parts and their libraries:
SparkFun-DiscreteSemi: Licensing: Creative Commons ShareAlike 4.0 International - https://creativecommons.org/licenses/by-sa/4.0
SparkFun-Aesthetics: Released under the Creative Commons Attribution Share-Alike 4.0 License
SparkFun-Aesthetics: https://creativecommons.org/licenses/by-sa/4.0
